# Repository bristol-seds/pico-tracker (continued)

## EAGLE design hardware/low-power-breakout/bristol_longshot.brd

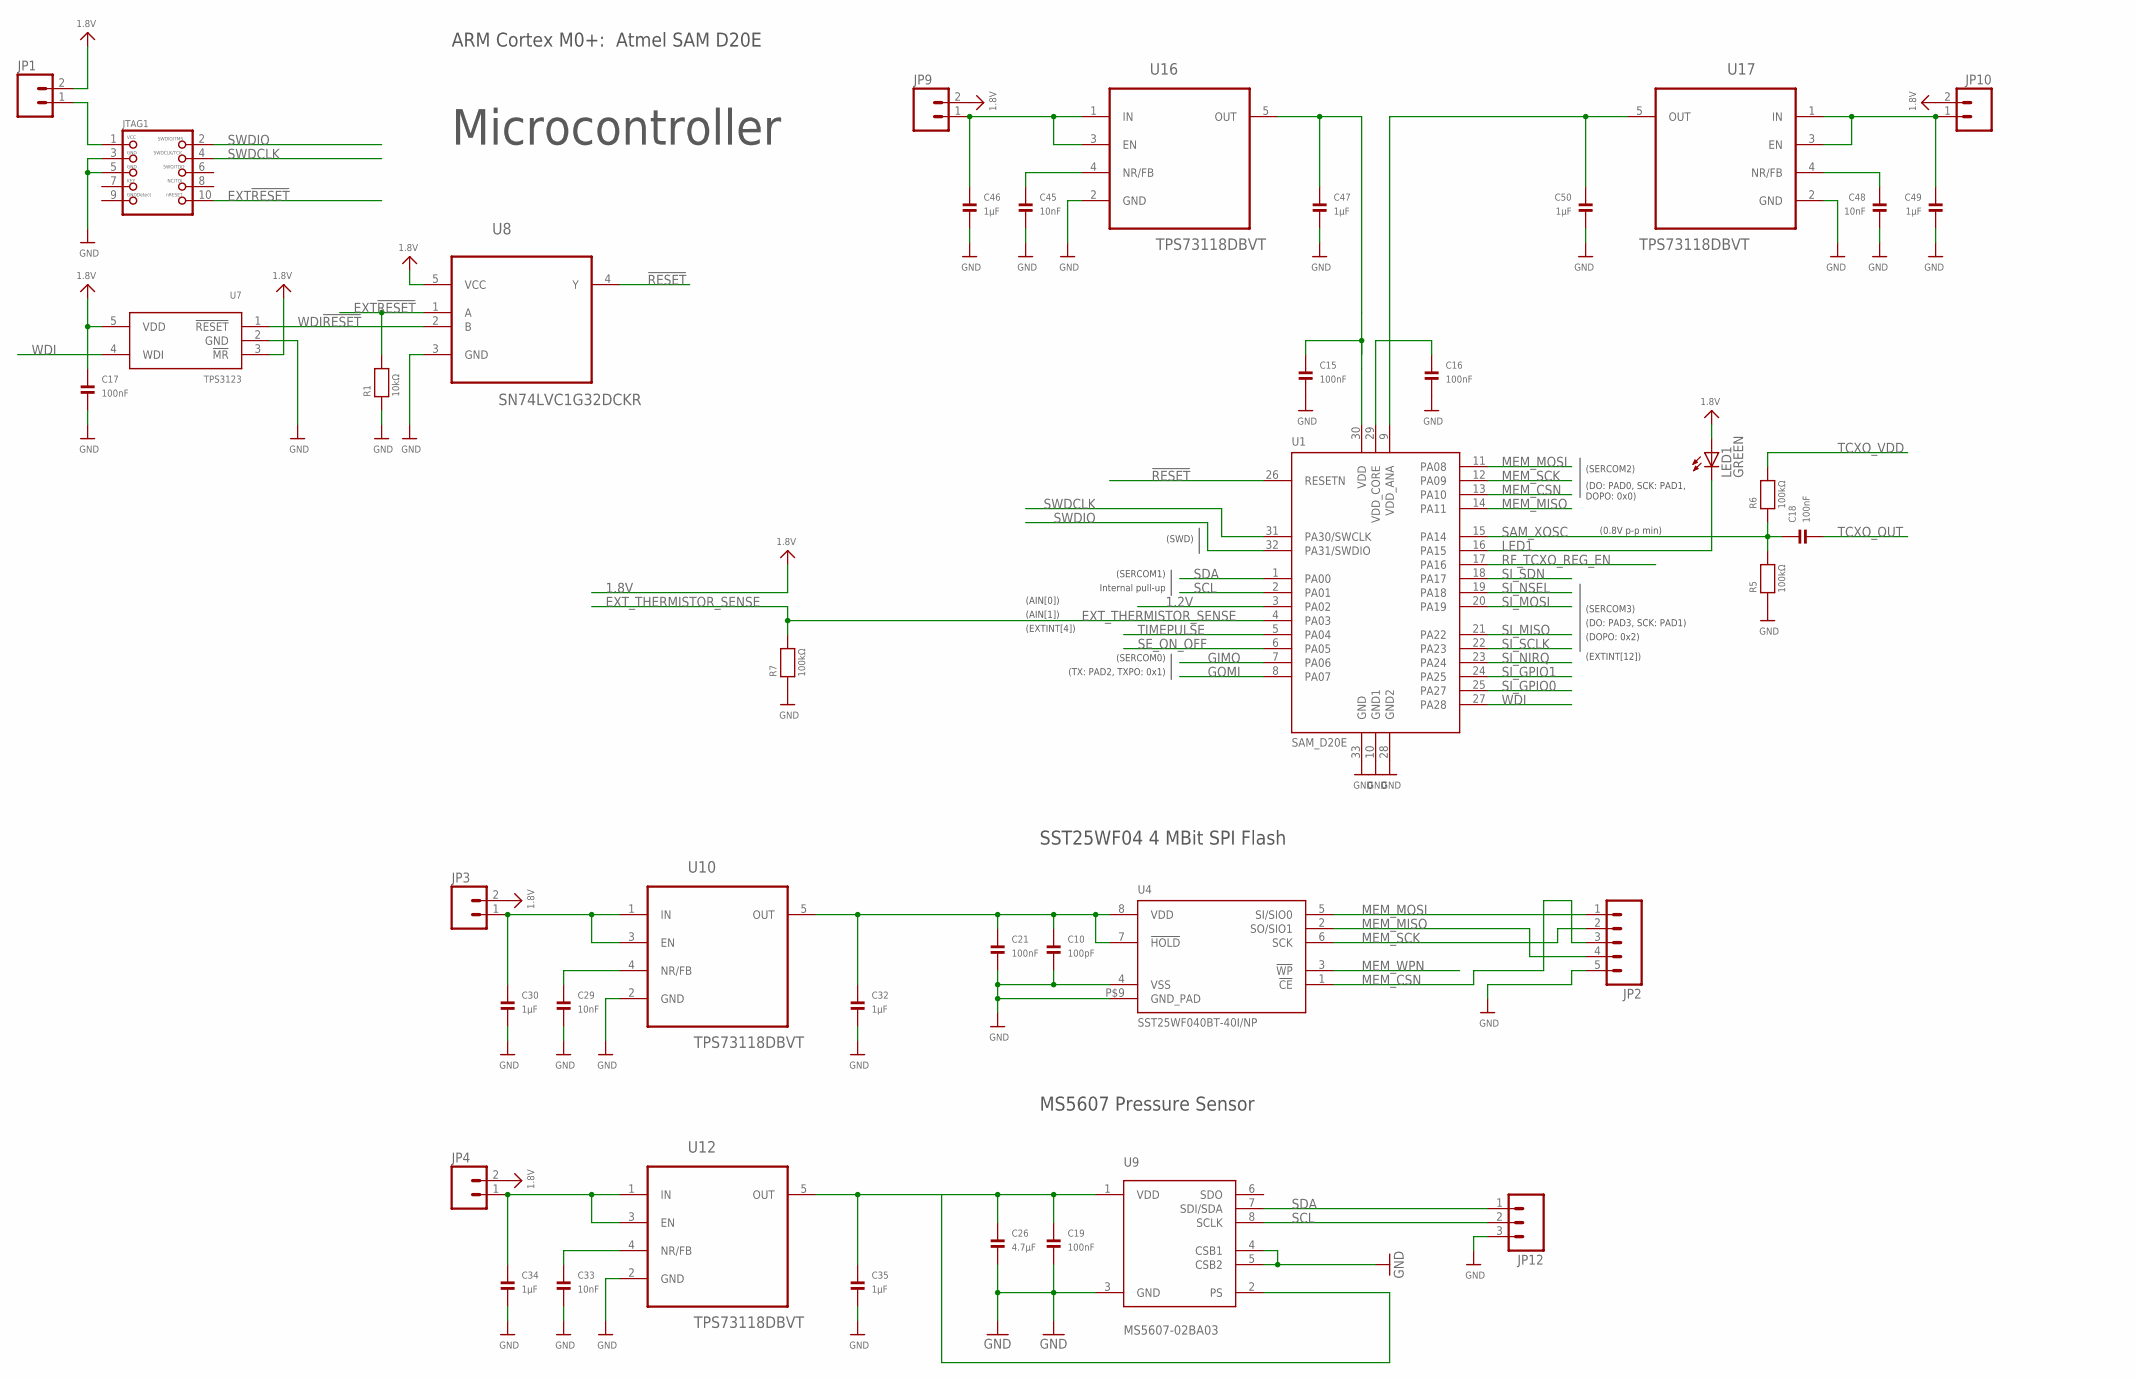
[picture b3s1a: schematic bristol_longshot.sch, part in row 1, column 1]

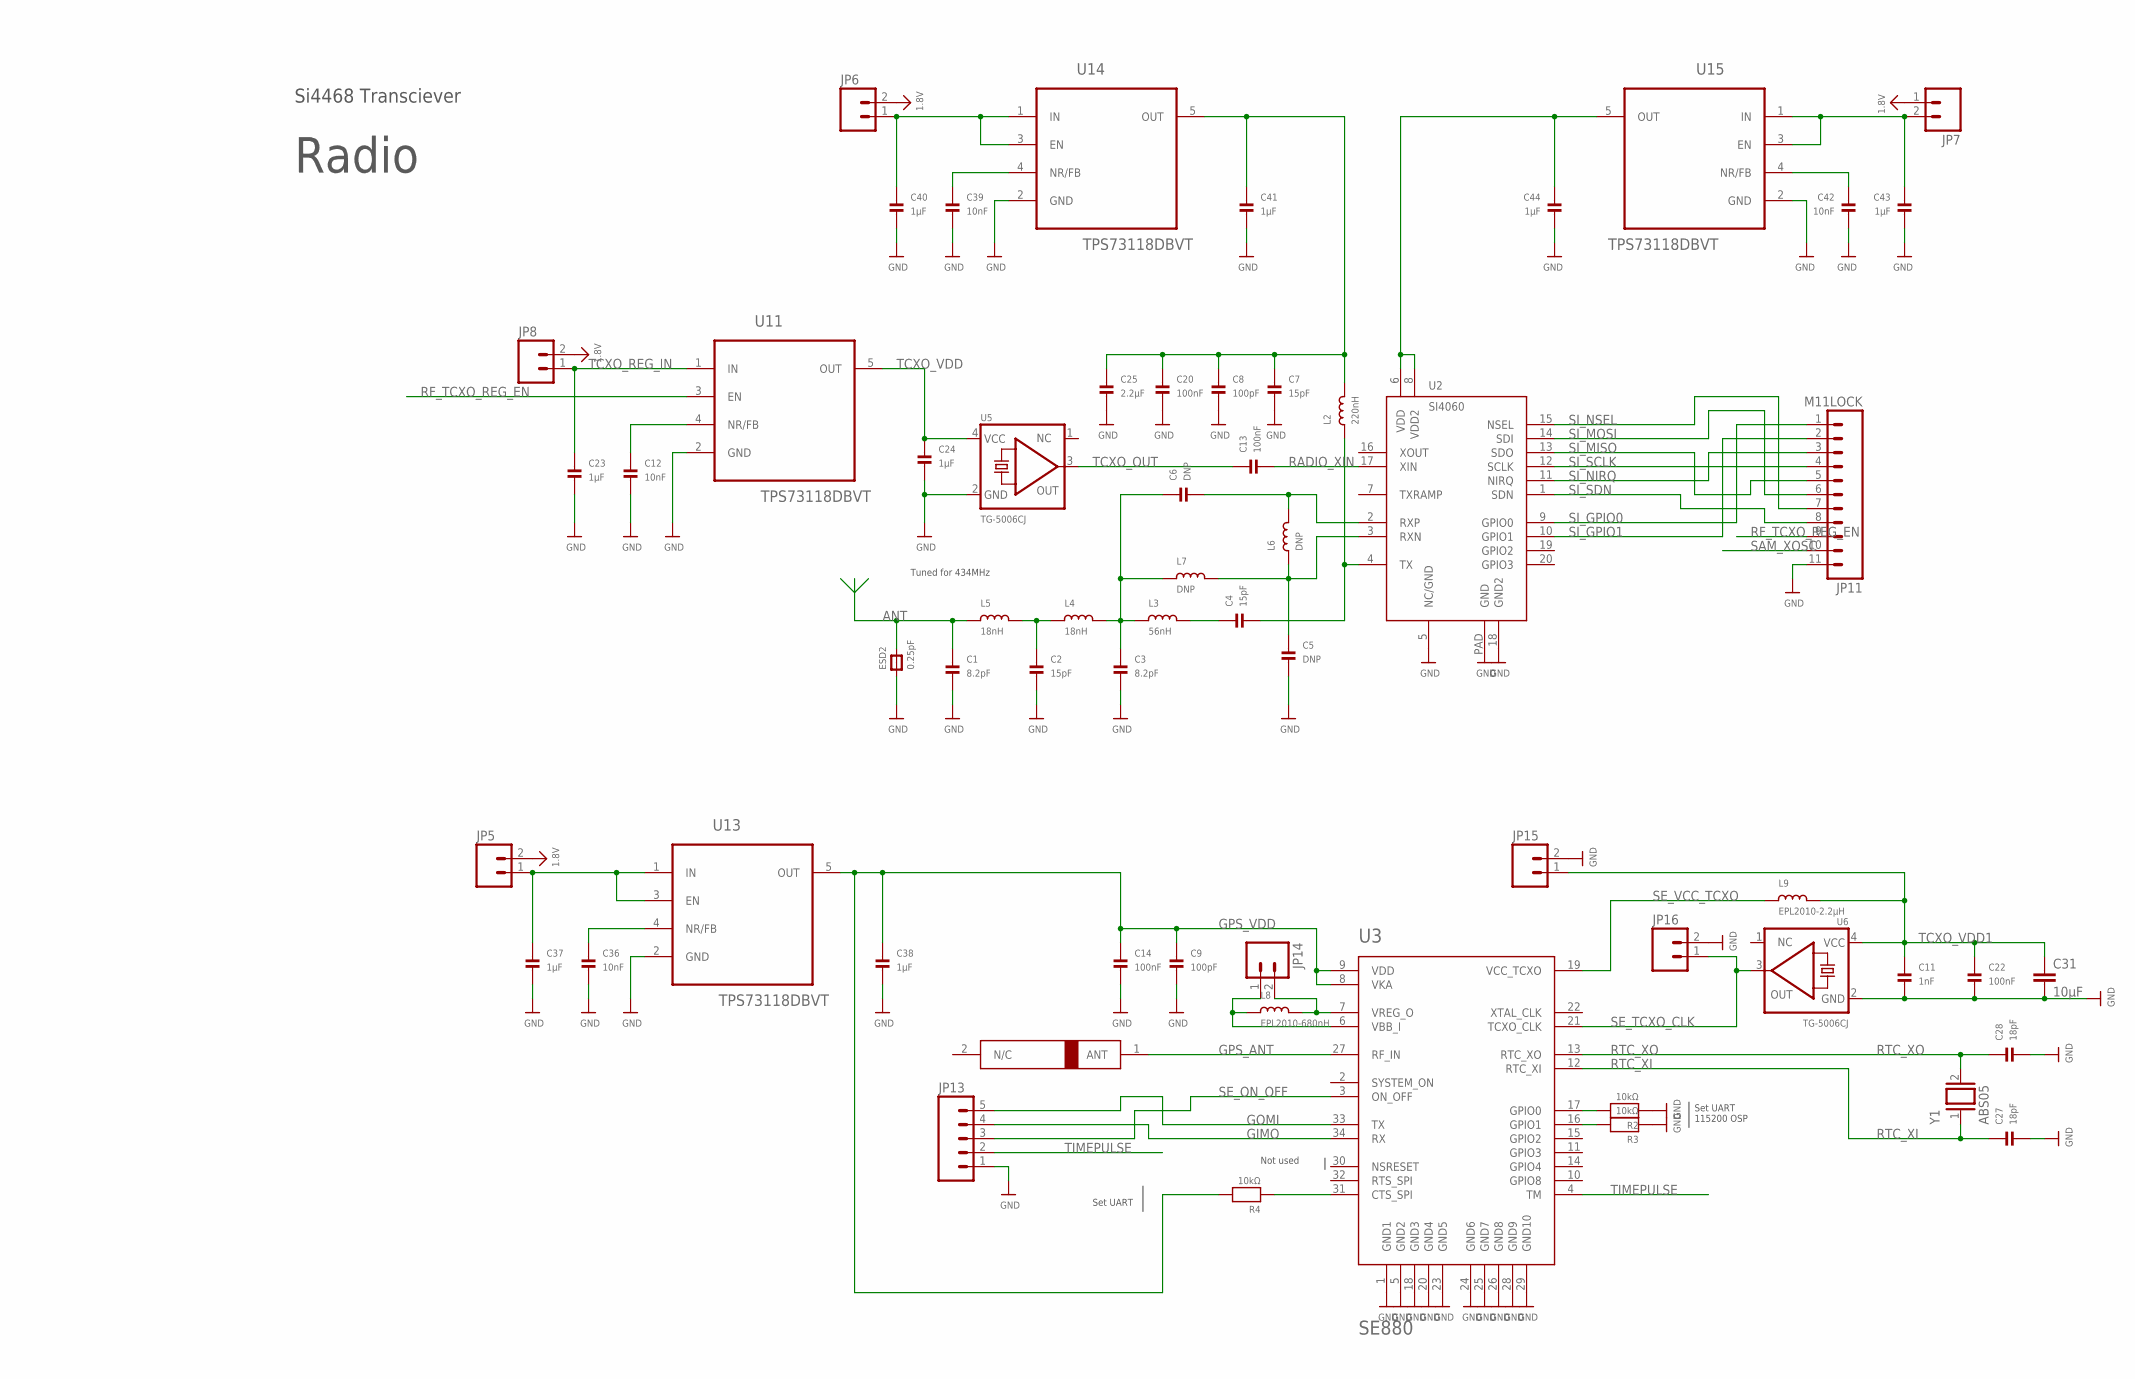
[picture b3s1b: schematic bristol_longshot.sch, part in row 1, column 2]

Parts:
A1: 1575AT43A40
C1, C3: 8.2pF; _0402@2
C2, C4, C7: 15pF; _0402@2
C5, C6: DNP; _0402@2
C8, C9, C10: 100pF; _0402@2
C11: 1nF; _0402@2
C12, C29, C33, C36, C39, C42, C45, C48: 10nF; _0402@2
C13, C14, C15, C16, C17, C18, C19, C20, C21, C22: 100nF; _0402@2
C23, C24, C30, C32, C34, C35, C37, C38, C40, C41, C43, C44, C46, C47, C49, C50: 1µF; _0402@2
C25: 2.2µF; _0402@2
C26: 4.7µF; _0402@2
C27, C28: 18pF; _0402@2
C31: 10µF; C0603K
ESD2: 0.25pF; _0603MP
JP1, JP3, JP4, JP5, JP6, JP7, JP8, JP9, JP10, JP14, JP15, JP16: M02LOCK; 1X02_LOCK
JP2, JP13: M05LOCK; 1X05_LOCK
JP11: M11LOCK; 1X11_LOCK
JP12: M03LOCK; 1X03_LOCK
JTAG1: JTAG-CORTEXM3SMT; 2X05_1.27MM_SMT
L2: 220nH; _0402@1
L3: 56nH; _0402@1
L4, L5: 18nH; _0402@1
L6, L7: DNP; _0402@1
L8: EPL2010-680nH; EPL2010
L9: EPL2010-2.2µH; EPL2010
LED1: GREEN; CHIPLED_0603
R1, R2, R3, R4: 10kΩ; _0402
R5, R6, R7: 100kΩ; _0402
U1: SAM_D20E; QFN32_5MM
U2: SI4060; QFN20
U3: SE880
U4: SST25WF040BT-40I/NP; USON-8
U5, U6: TG-5006CJ; TC-5006CJ
U7: TPS3123; SOT23-5
U8: SN74LVC1G32DCKR; SOT65P210X110-5N
U9: MS5607-02BA03
U10, U11, U12, U13, U14, U15, U16, U17: TPS73118DBVT; SOT95P280X145-5N
Y1: ABS05

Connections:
1.2V: U1.3 (PA02)
1.8V: C17.1, JP1.2, JP3.2, JP4.2, JP5.2, JP6.2, JP7.1, JP8.2, JP9.2, JP10.2, LED1.A, U7.3 (!MR), U7.5 (VDD), U8.5 (VCC)
!RESET: U1.26 (RESETN), U8.4 (Y)
ANT: C1.1, ESD2.2, L5.1
EXT!RESET: JTAG1.10, R1.2, U8.1 (A)
EXT_THERMISTOR_SENSE: R7.2, U1.4 (PA03)
FILTER1: C3.1, C6.1, L3.1, L4.2, L7.1
FILTER2: C2.1, L4.1, L5.2
GIMO: JP13.4, U1.7 (PA06), U3.34 (RX)
GND: C1.2, C2.2, C3.2, C5.2, C7.2, C8.2, C9.2, C10.2, C11.2, C12.2, C14.2, C15.2, C16.2, C17.2, C19.2, C20.2, C21.2, C22.2, C23.2, C24.2, C25.2, C26.2, C27.2, C28.2, C29.2, C30.2, C31.2, C32.2, C33.2, C34.2, C35.2, C36.2, C37.2, C38.2, C39.2, C40.2, C41.2, C42.2, C43.2, C44.2, C45.2, C46.2, C47.2, C48.2, C49.2, C50.2, ESD2.1, JP2.5, JP11.11, JP12.3, JP13.1, JP15.2, JP16.2, JTAG1.3, JTAG1.5, R1.1, R2.1, R3.1, R5.1, R7.1, U1.10 (GND1), U1.28 (GND2), U1.33 (GND), U2.5 (NC/GND), U2.18 (GND2), U2.PAD (GND), U3.1 (GND1), U3.5 (GND2), U3.18 (GND3), U3.20 (GND4), U3.23 (GND5), U3.24 (GND6), U3.25 (GND7), U3.26 (GND8), U3.28 (GND9), U3.29 (GND10), U4.4 (VSS), U4.P$9 (GND_PAD), U5.2 (GND), U6.2 (GND), U7.2 (GND), U8.3 (GND), U9.3 (GND), U9.4 (CSB1), U9.5 (CSB2), U10.2 (GND), U11.2 (GND), U12.2 (GND), U13.2 (GND), U14.2 (GND), U15.2 (GND), U16.2 (GND), U17.2 (GND)
GOMI: JP13.5, U1.8 (PA07), U3.33 (TX)
GPS_ANT: A1.1 (ANT), U3.27 (RF_IN)
GPS_VDD: C9.1, C14.1, C38.1, R4.2, U3.8 (VKA), U3.9 (VDD), U13.5 (OUT)
LED1: LED1.C, U1.16 (PA15)
MEM_CSN: JP2.3, U1.13 (PA10), U4.1 (!CE)
MEM_MISO: JP2.4, U1.14 (PA11), U4.2 (SO/SIO1)
MEM_MOSI: JP2.1, U1.11 (PA08), U4.5 (SI/SIO0)
MEM_SCK: JP2.2, U1.12 (PA09), U4.6 (SCK)
MEM_WPN: U4.3 (!WP)
unnamed: JP1.1, JTAG1.1
unnamed: C30.1, JP3.1, U10.1 (IN), U10.3 (EN)
unnamed: C29.1, U10.4 (NR/FB)
unnamed: C10.1, C21.1, C32.1, U4.7 (!HOLD), U4.8 (VDD), U10.5 (OUT)
unnamed: C34.1, JP4.1, U12.1 (IN), U12.3 (EN)
unnamed: C33.1, U12.4 (NR/FB)
unnamed: C19.1, C26.1, C35.1, U9.1 (VDD), U9.2 (PS), U12.5 (OUT)
unnamed: C37.1, JP5.1, U13.1 (IN), U13.3 (EN)
unnamed: C36.1, U13.4 (NR/FB)
unnamed: C46.1, JP9.1, U16.1 (IN), U16.3 (EN)
unnamed: C40.1, JP6.1, U14.1 (IN), U14.3 (EN)
unnamed: C39.1, U14.4 (NR/FB)
unnamed: C45.1, U16.4 (NR/FB)
unnamed: C43.1, JP7.2, U15.1 (IN), U15.3 (EN)
unnamed: C42.1, U15.4 (NR/FB)
unnamed: C44.1, U2.6 (VDD), U2.8 (VDD2), U15.5 (OUT)
unnamed: C15.1, C47.1, U1.30 (VDD), U16.5 (OUT)
unnamed: C49.1, JP10.1, U17.1 (IN), U17.3 (EN)
unnamed: C48.1, U17.4 (NR/FB)
unnamed: C50.1, U1.9 (VDD_ANA), U17.5 (OUT)
RADIO_VDD: C7.1, C8.1, C20.1, C25.1, C41.1, L2.2, U14.5 (OUT)
RADIO_XIN: C13.2, U2.17 (XIN)
RF_OUT: C4.2, L2.1, U2.4 (TX)
RF_TANK: C4.1, L3.2
RF_TCXO_REG_EN: JP11.9, U1.17 (PA16), U11.3 (EN)
RTC_XI: C27.1, U3.12 (RTC_XI), Y1.1
RTC_XO: C28.1, U3.13 (RTC_XO), Y1.2
RXN: C5.1, L6.1, L7.2, U2.3 (RXN)
RXP: C6.2, L6.2, U2.2 (RXP)
SAM_XOSC: C18.1, JP11.10, R5.2, R6.1, U1.15 (PA14)
SCL: JP12.2, U1.2 (PA01), U9.8 (SCLK)
SDA: JP12.1, U1.1 (PA00), U9.7 (SDI/SDA)
SE_GPIO0: R2.2, U3.17 (GPIO0)
SE_GPIO1: R3.2, U3.16 (GPIO1)
SE_MODE_PULL: R4.1, U3.31 (CTS_SPI)
SE_ON_OFF: JP13.3, U1.6 (PA05), U3.3 (ON_OFF)
SE_TCXO_CLK: JP16.1, U3.21 (TCXO_CLK), U6.3 (OUT)
SE_VBB: JP14.1, L8.1, U3.6 (VBB_I)
SE_VCC_TCXO: L9.1, U3.19 (VCC_TCXO)
SE_VREG: JP14.2, L8.2, U3.7 (VREG_O)
SI_GPIO0: JP11.1, U1.25 (PA27), U2.9 (GPIO0)
SI_GPIO1: JP11.2, U1.24 (PA25), U2.10 (GPIO1)
SI_MISO: JP11.5, U1.21 (PA22), U2.13 (SDO)
SI_MOSI: JP11.6, U1.20 (PA19), U2.14 (SDI)
SI_NIRQ: JP11.3, U1.23 (PA24), U2.11 (NIRQ)
SI_NSEL: JP11.7, U1.19 (PA18), U2.15 (NSEL)
SI_SCLK: JP11.4, U1.22 (PA23), U2.12 (SCLK)
SI_SDN: JP11.8, U1.18 (PA17), U2.1 (SDN)
SWDCLK: JTAG1.4, U1.31 (PA30/SWCLK)
SWDIO: JTAG1.2, U1.32 (PA31/SWDIO)
TCXO_OUT: C13.1, C18.2, U5.3 (OUT)
TCXO_REG_IN: C23.1, JP8.1, U11.1 (IN)
TCXO_REG_NR: C12.1, U11.4 (NR/FB)
TCXO_VDD: C24.1, R6.2, U5.4 (VCC), U11.5 (OUT)
TCXO_VDD1: C11.1, C22.1, C31.1, JP15.1, L9.2, U6.4 (VCC)
TIMEPULSE: JP13.2, U1.5 (PA04), U3.4 (TM)
VDD_CORE: C16.1, U1.29 (VDD_CORE)
WDI: U1.27 (PA28), U7.4 (WDI)
WDI!RESET: U7.1 (!RESET), U8.2 (B)

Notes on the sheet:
ARM Cortex M0+: Atmel SAM D20E
(SERCOM3)
(SWD)
(EXTINT[12])
(DO: PAD3, SCK: PAD1)
(DOPO: 0x2)
(SERCOM2)
(DO: PAD0, SCK: PAD1, DOPO: 0x0)
(SERCOM0)
(TX: PAD2, TXPO: 0x1)
SST25WF04 4 MBit SPI Flash
Si4468 Transciever
Tuned for 434MHz
Radio
(0.8V p-p min)
(AIN[1])
(EXTINT[4])
(SERCOM1)
MS5607 Pressure Sensor
Microcontroller
Set UART 115200 OSP
Set UART
Internal pull-up
(AIN[0])
Not used

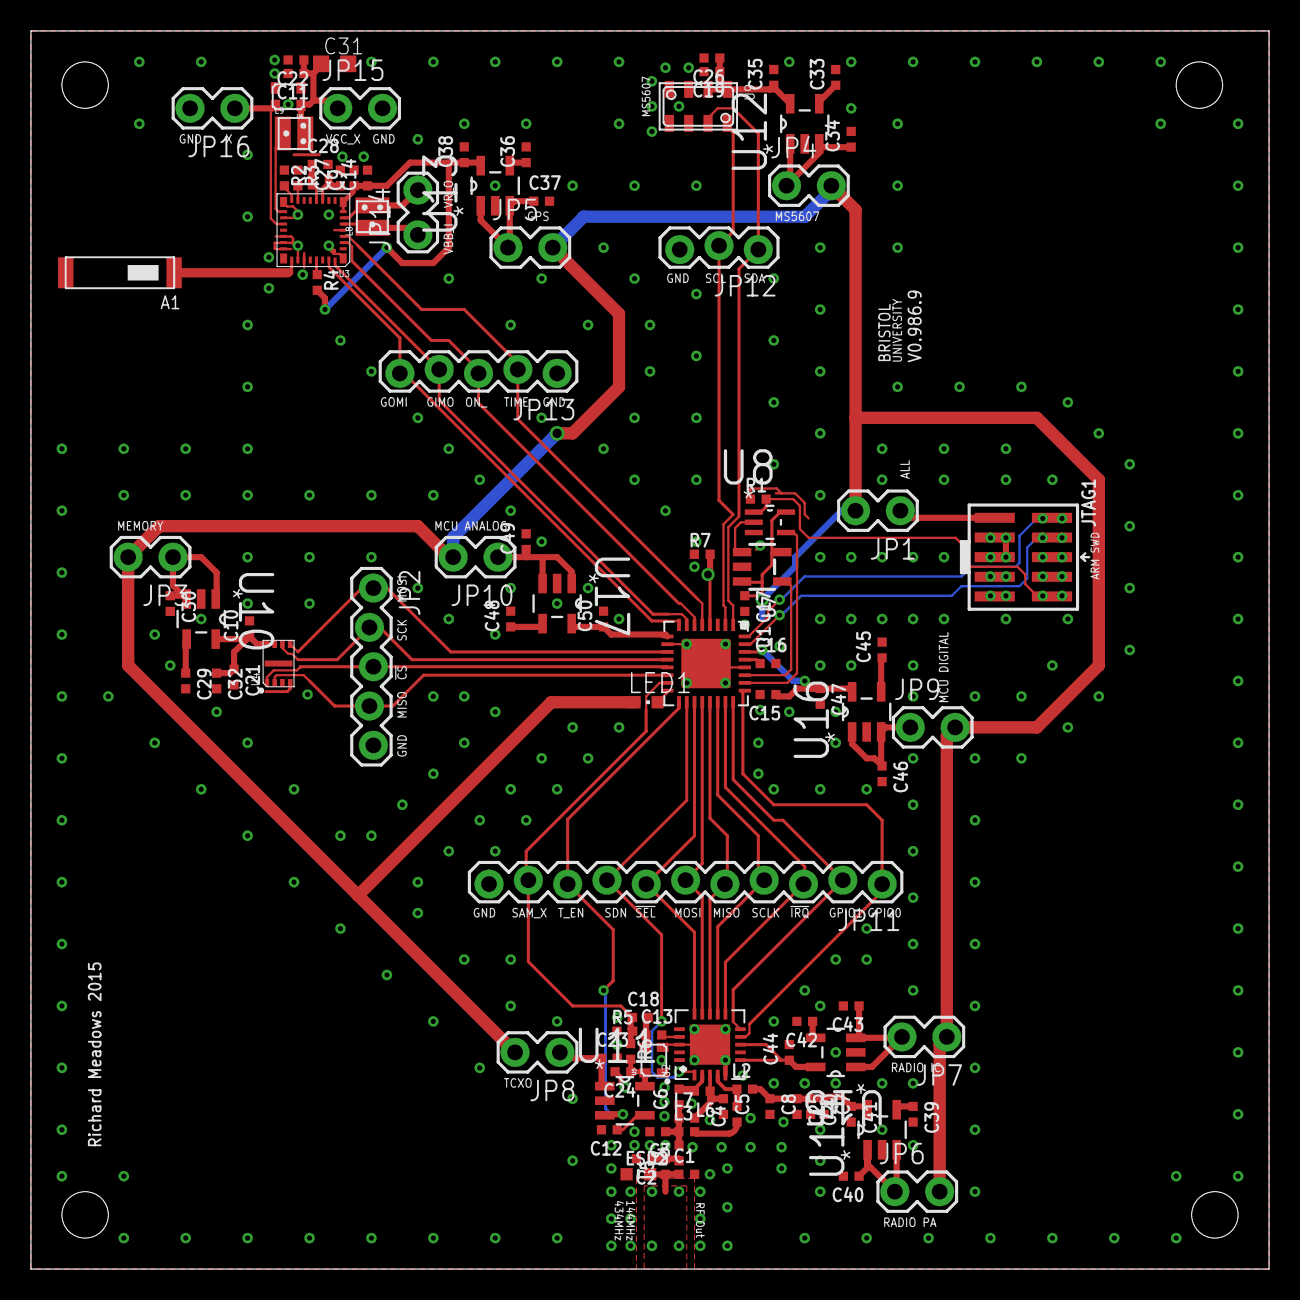
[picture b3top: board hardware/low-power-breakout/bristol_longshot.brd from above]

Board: 2 copper layers, 80.0 x 80.0 mm, 103 parts (0 on the bottom side), 76 nets.

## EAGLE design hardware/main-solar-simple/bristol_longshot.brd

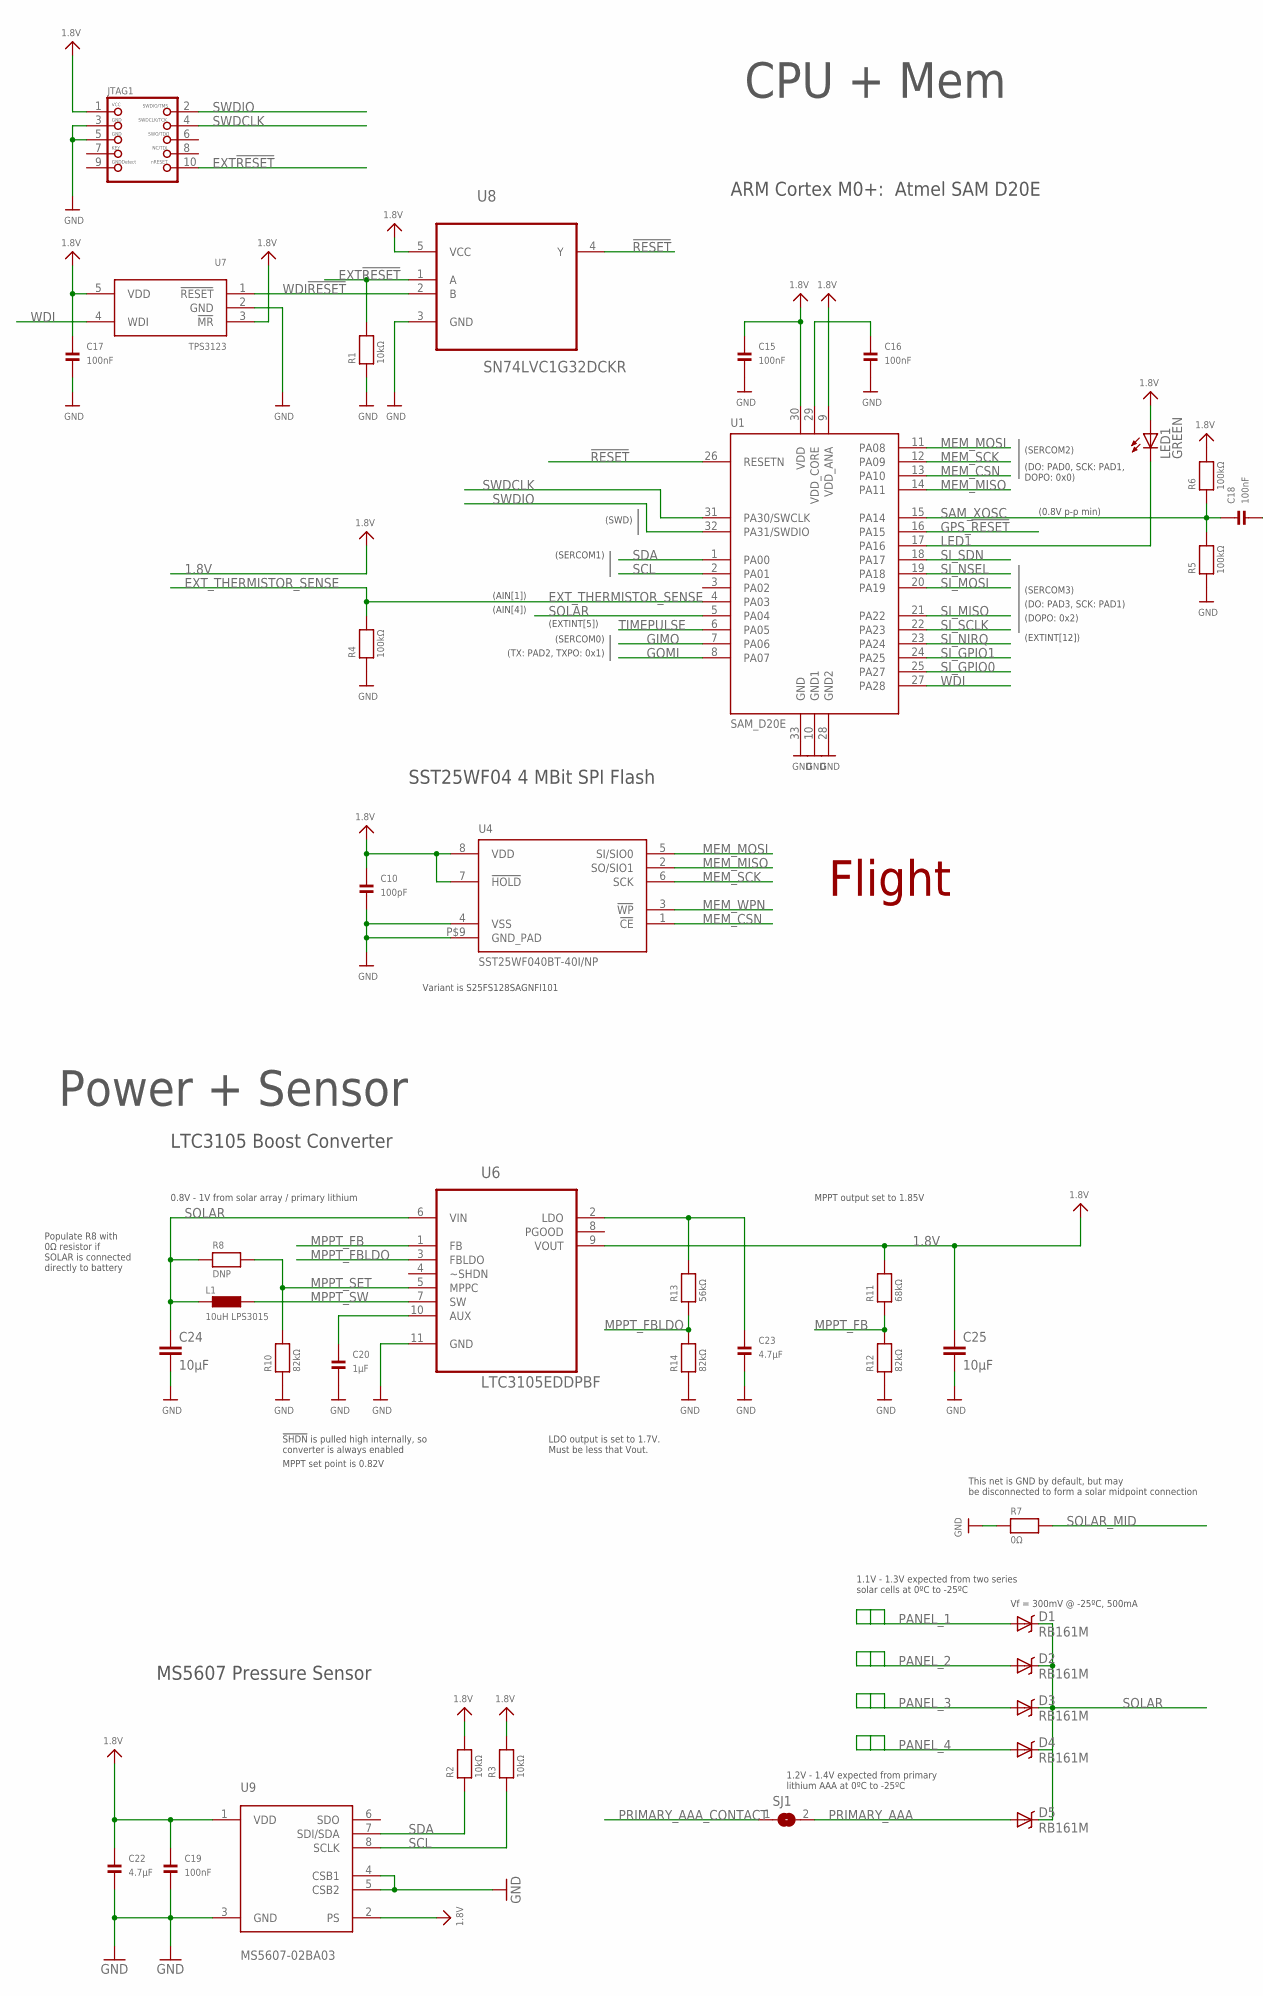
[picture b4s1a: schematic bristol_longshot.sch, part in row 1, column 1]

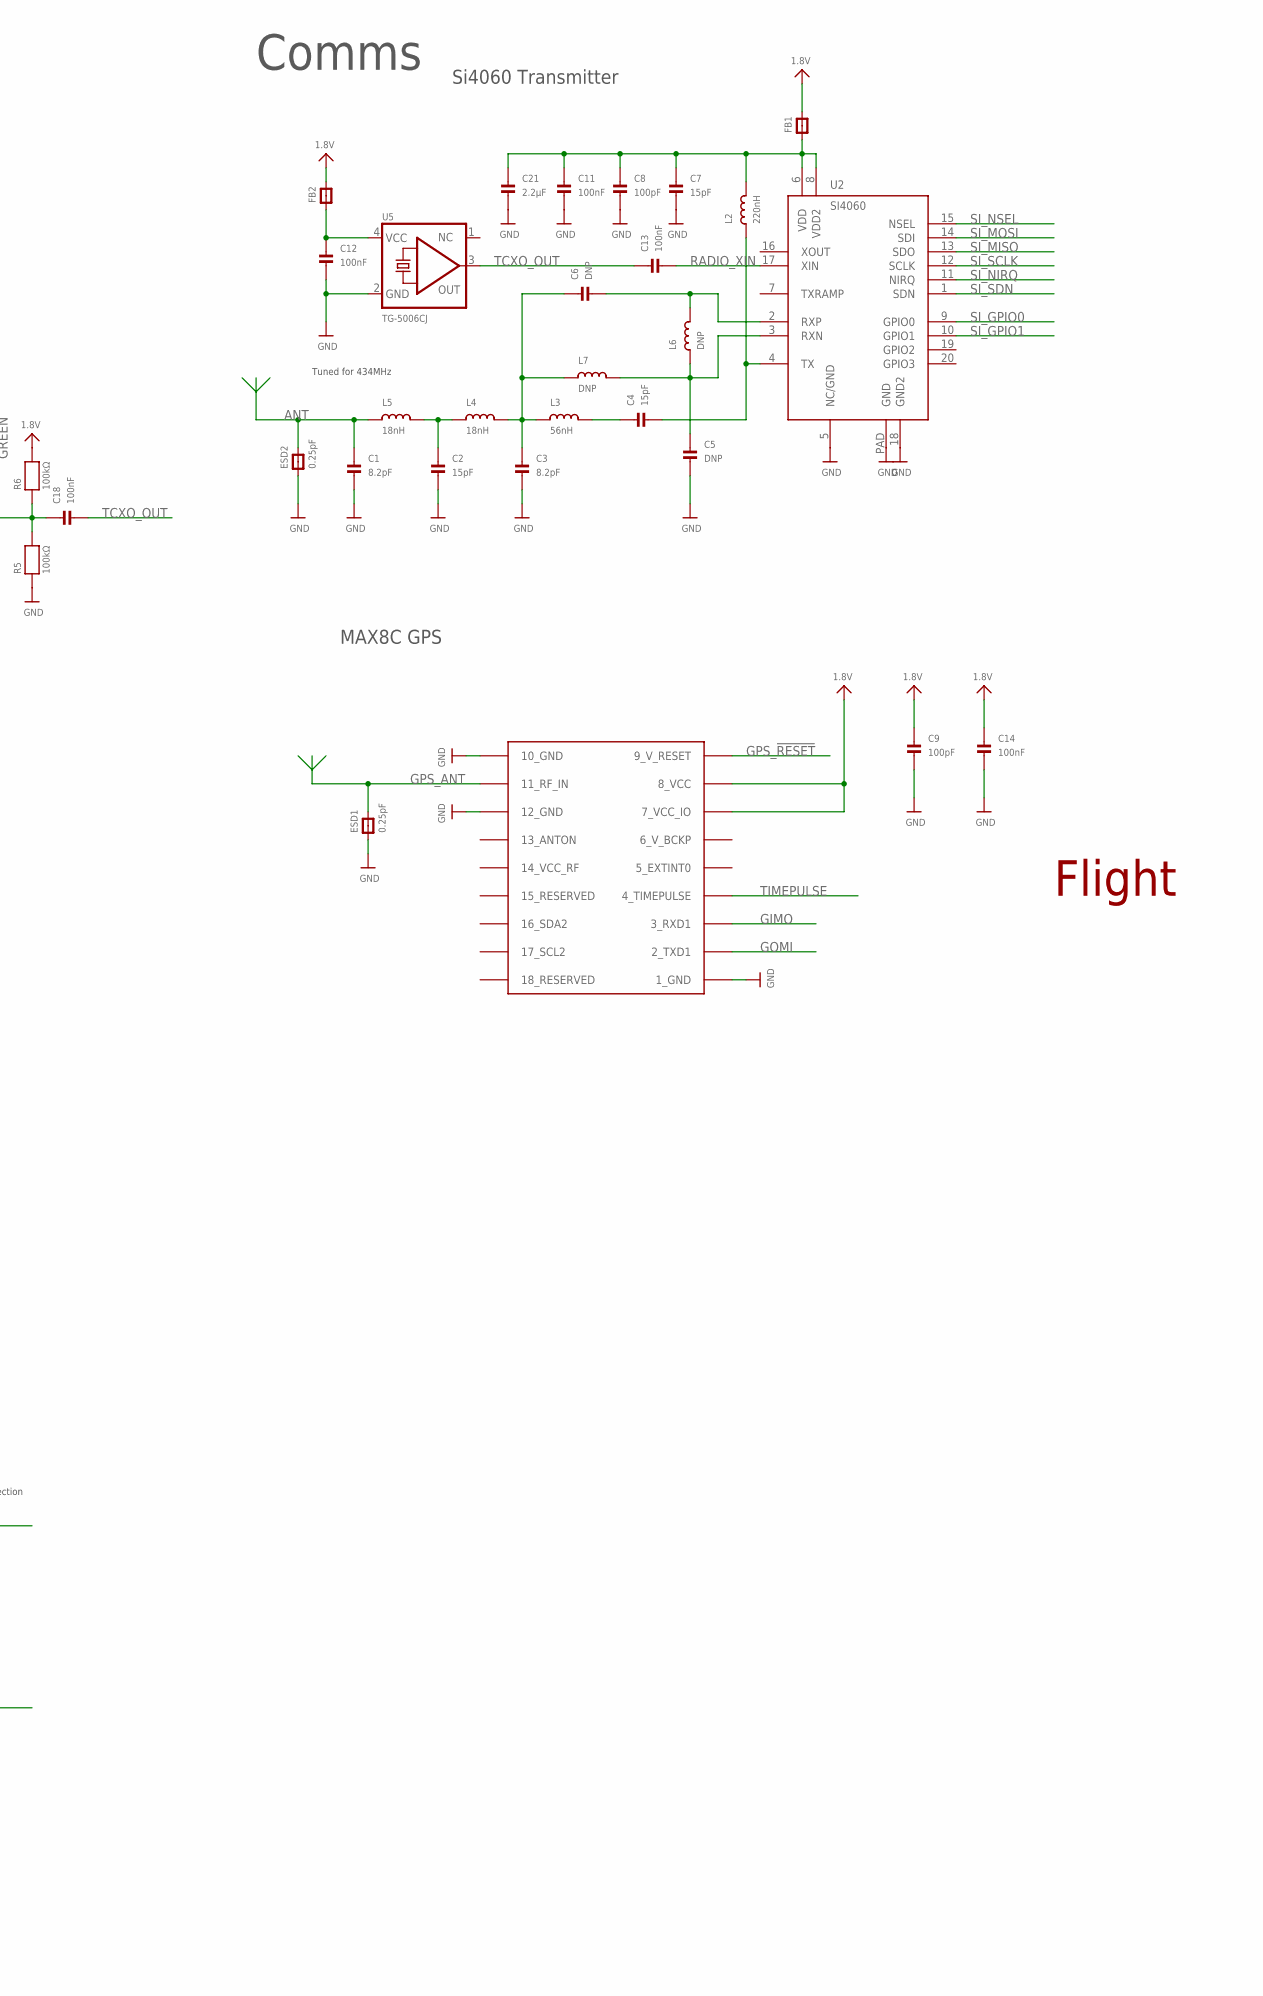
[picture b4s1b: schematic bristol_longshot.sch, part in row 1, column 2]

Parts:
C1, C3: 8.2pF; _0402@1
C2, C4, C7: 15pF; _0402@1
C5, C6: DNP; _0402@1
C8, C9, C10: 100pF; _0402@1
C11, C12, C13, C14, C15, C16, C17, C18, C19: 100nF; _0402@1
C20: 1µF; _0402@1
C21: 2.2µF; _0402@1
C22, C23: 4.7µF; _0402@1
C24, C25: 10µF; C0603K
D1, D2, D3, D4, D5: RB161M
ESD1, ESD2: 0.25pF; _0603MP
FB1, FB2: FERRITE_0402; _0402@1
JTAG1: JTAG-CORTEXM3SMT; 2X05_1.27MM_SMT
L1: 10uH LPS3015; LPS3015
L2: 220nH; _0402@1
L3: 56nH; _0402@1
L4, L5: 18nH; _0402@1
L6, L7: DNP; _0402@1
LED1: GREEN; CHIPLED_0603
R1, R2, R3: 10kΩ; _0402
R4, R5, R6: 100kΩ; _0402
R7: 0Ω; _0402
R8: DNP; _0402
R10, R12, R14: 82kΩ; _0402
R11: 68kΩ; _0402
R13: 56kΩ; _0402
SJ1: SOLDERJUMPERREFLOW; SOLDERJUMPER_REFLOW
U1: SAM_D20E; QFN32_5MM
U2: SI4060; QFN20
U3: UBLOX_MAX
U4: SST25WF040BT-40I/NP; USON-8
U5: TG-5006CJ; TC-5006CJ
U6: LTC3105EDDPBF; DFN300X300X80-11N
U7: TPS3123; SOT23-5
U8: SN74LVC1G32DCKR; SOT65P210X110-5N
U9: MS5607-02BA03

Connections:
1.8V: C9.1, C10.1, C14.1, C15.1, C17.1, C19.1, C22.1, C25.1, FB1.2, FB2.2, JTAG1.1, LED1.A, R2.2, R3.2, R6.2, R11.2, U1.9 (VDD_ANA), U1.30 (VDD), U3.7_VCC_IO, U3.8_VCC, U4.7 (!HOLD), U4.8 (VDD), U6.9 (VOUT), U7.3 (!MR), U7.5 (VDD), U8.5 (VCC), U9.1 (VDD), U9.2 (PS)
!RESET: U1.26 (RESETN), U8.4 (Y)
ANT: C1.1, ESD2.2, L5.1
EXT!RESET: JTAG1.10, R1.2, U8.1 (A)
EXT_THERMISTOR_SENSE: R4.2, U1.4 (PA03)
FILTER1: C3.1, C6.1, L3.1, L4.2, L7.1
FILTER2: C2.1, L4.1, L5.2
GIMO: U1.7 (PA06), U3.3_RXD1
GND: C1.2, C2.2, C3.2, C5.2, C7.2, C8.2, C9.2, C10.2, C11.2, C12.2, C14.2, C15.2, C16.2, C17.2, C19.2, C20.2, C21.2, C22.2, C23.2, C24.2, C25.2, ESD1.1, ESD2.1, JTAG1.3, JTAG1.5, R1.1, R4.1, R5.1, R7.1, R10.1, R12.1, R14.1, U1.10 (GND1), U1.28 (GND2), U1.33 (GND), U2.5 (NC/GND), U2.18 (GND2), U2.PAD (GND), U3.1_GND, U3.10_GND, U3.12_GND, U4.4 (VSS), U4.P$9 (GND_PAD), U5.2 (GND), U6.11 (GND), U7.2 (GND), U8.3 (GND), U9.3 (GND), U9.4 (CSB1), U9.5 (CSB2)
GOMI: U1.8 (PA07), U3.2_TXD1
GPS_!RESET: U1.16 (PA15), U3.9_V_RESET
GPS_ANT: ESD1.2, U3.11_RF_IN
LED1: LED1.C, U1.17 (PA16)
MEM_CSN: U1.13 (PA10), U4.1 (!CE)
MEM_MISO: U1.14 (PA11), U4.2 (SO/SIO1)
MEM_MOSI: U1.11 (PA08), U4.5 (SI/SIO0)
MEM_SCK: U1.12 (PA09), U4.6 (SCK)
MEM_WPN: U4.3 (!WP)
MPPT_AUX: C20.1, U6.10 (AUX)
MPPT_FB: R11.1, R12.2, U6.1 (FB)
MPPT_FBLDO: R13.1, R14.2, U6.3 (FBLDO)
MPPT_LDO: C23.1, R13.2, U6.2 (LDO)
MPPT_SET: R8.2, R10.2, U6.5 (MPPC)
MPPT_SW: L1.2_1 (2), L1.2_2 (2), L1.2_3 (2), L1.2_4 (2), L1.2_5 (2), L1.2_6 (2), L1.2_7 (2), L1.2_8 (2), L1.2_9 (2), U6.7 (SW)
PANEL_1: D1.ANODE (A)
PANEL_2: D2.ANODE (A)
PANEL_3: D3.ANODE (A)
PANEL_4: D4.ANODE (A)
PRIMARY_AAA: D5.ANODE (A), SJ1.2
PRIMARY_AAA_CONTACT: SJ1.1
RADIO_VDD: C7.1, C8.1, C11.1, C21.1, FB1.1, L2.2, U2.6 (VDD), U2.8 (VDD2)
RADIO_XIN: C13.2, U2.17 (XIN)
RF_OUT: C4.2, L2.1, U2.4 (TX)
RF_TANK: C4.1, L3.2
RXN: C5.1, L6.1, L7.2, U2.3 (RXN)
RXP: C6.2, L6.2, U2.2 (RXP)
SAM_XOSC: C18.1, R5.2, R6.1, U1.15 (PA14)
SCL: R3.1, U1.2 (PA01), U9.8 (SCLK)
SDA: R2.1, U1.1 (PA00), U9.7 (SDI/SDA)
SI_GPIO0: U1.25 (PA27), U2.9 (GPIO0)
SI_GPIO1: U1.24 (PA25), U2.10 (GPIO1)
SI_MISO: U1.21 (PA22), U2.13 (SDO)
SI_MOSI: U1.20 (PA19), U2.14 (SDI)
SI_NIRQ: U1.23 (PA24), U2.11 (NIRQ)
SI_NSEL: U1.19 (PA18), U2.15 (NSEL)
SI_SCLK: U1.22 (PA23), U2.12 (SCLK)
SI_SDN: U1.18 (PA17), U2.1 (SDN)
SOLAR: C24.1, D1.CATHODE (C), D2.CATHODE (C), D3.CATHODE (C), D4.CATHODE (C), D5.CATHODE (C), L1.1_1 (1), L1.1_2 (1), L1.1_3 (1), L1.1_4 (1), L1.1_5 (1), L1.1_6 (1), L1.1_7 (1), L1.1_8 (1), L1.1_9 (1), R8.1, U1.5 (PA04), U6.6 (VIN)
SOLAR_MID: R7.2
SWDCLK: JTAG1.4, U1.31 (PA30/SWCLK)
SWDIO: JTAG1.2, U1.32 (PA31/SWDIO)
TCXO_OUT: C13.1, C18.2, U5.3 (OUT)
TCXO_VDD: C12.1, FB2.1, U5.4 (VCC)
TIMEPULSE: U1.6 (PA05), U3.4_TIMEPULSE
VDD_CORE: C16.1, U1.29 (VDD_CORE)
WDI: U1.27 (PA28), U7.4 (WDI)
WDI!RESET: U7.1 (!RESET), U8.2 (B)

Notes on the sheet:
ARM Cortex M0+: Atmel SAM D20E
(SERCOM3)
(SWD)
(EXTINT[12])
(DO: PAD3, SCK: PAD1)
(DOPO: 0x2)
(SERCOM2)
(DO: PAD0, SCK: PAD1, DOPO: 0x0)
(SERCOM0)
(TX: PAD2, TXPO: 0x1)
SST25WF04 4 MBit SPI Flash
Variant is S25FS128SAGNFI101
MAX8C GPS
Si4060 Transmitter
Tuned for 434MHz
CPU + Mem
Comms
Flight
(EXTINT[5])
(0.8V p-p min)
(AIN[1])
(AIN[4])
(SERCOM1)
!SHDN! is pulled high internally, so converter is always enabled
MPPT set point is 0.82V
1.1V - 1.3V expected from two series solar cells at 0ºC to -25ºC
Vf = 300mV @ -25ºC, 500mA
0.8V - 1V from solar array / primary lithium
MPPT output set to 1.85V
LDO output is set to 1.7V. Must be less that Vout.
1.2V - 1.4V expected from primary lithium AAA at 0ºC to -25ºC
This net is GND by default, but may be disconnected to form a solar midpoint connection
LTC3105 Boost Converter
MS5607 Pressure Sensor
Power + Sensor
Populate R8 with 0Ω resistor if SOLAR is connected directly to battery
